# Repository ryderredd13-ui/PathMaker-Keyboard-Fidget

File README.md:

# PathMaker Keyboard Fidget
A Custom Keyboard fidget following the pathfinder guide renamed the PathMaker (Super original right?)
Anywayss... my spin on this project was to make it customizable!! i made a custom 3d case with extra space for stickers! I also added an extra button and led for extra fidget-ness :3

Here are some pics-

And heres my BOM-
[text](../../../Downloads/PathMaker-BOM.md)

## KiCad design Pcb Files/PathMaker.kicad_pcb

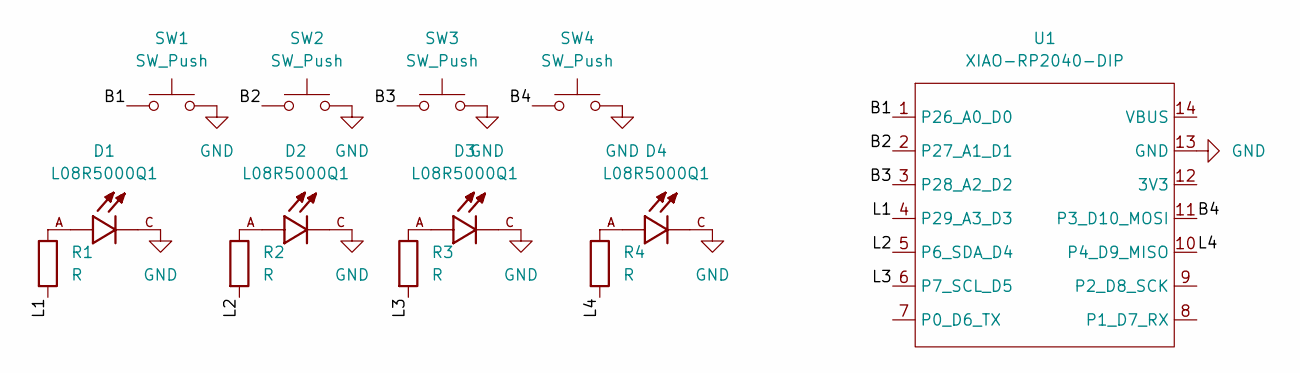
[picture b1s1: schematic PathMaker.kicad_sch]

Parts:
D1, D2, D3, D4: L08R5000Q1; LEDRD254W57D500H1070; PARTREV NA
R1, R2, R3, R4: R; R_Axial_DIN0204_L3.6mm_D1.6mm_P5.08mm_Horizontal
SW1, SW2, SW3, SW4: SW_Push; SW_Cherry_MX_1.00u_PCB
U1: XIAO-RP2040-DIP

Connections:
/B1: SW1.1, U1.1 (P26_A0_D0)
/B2: SW2.1, U1.2 (P27_A1_D1)
/B3: SW3.1, U1.3 (P28_A2_D2)
/B4: SW4.1, U1.11 (P3_D10_MOSI)
/L1: R1.2, U1.4 (P29_A3_D3)
/L2: R2.2, U1.5 (P6_SDA_D4)
/L3: R3.2, U1.6 (P7_SCL_D5)
/L4: R4.2, U1.10 (P4_D9_MISO)
GND: D1.C, D2.C, D3.C, D4.C, SW1.2, SW2.2, SW3.2, SW4.2, U1.13 (GND)
unnamed: D1.A, R1.1
unnamed: D2.A, R2.1
unnamed: D3.A, R3.1
unnamed: D4.A, R4.1

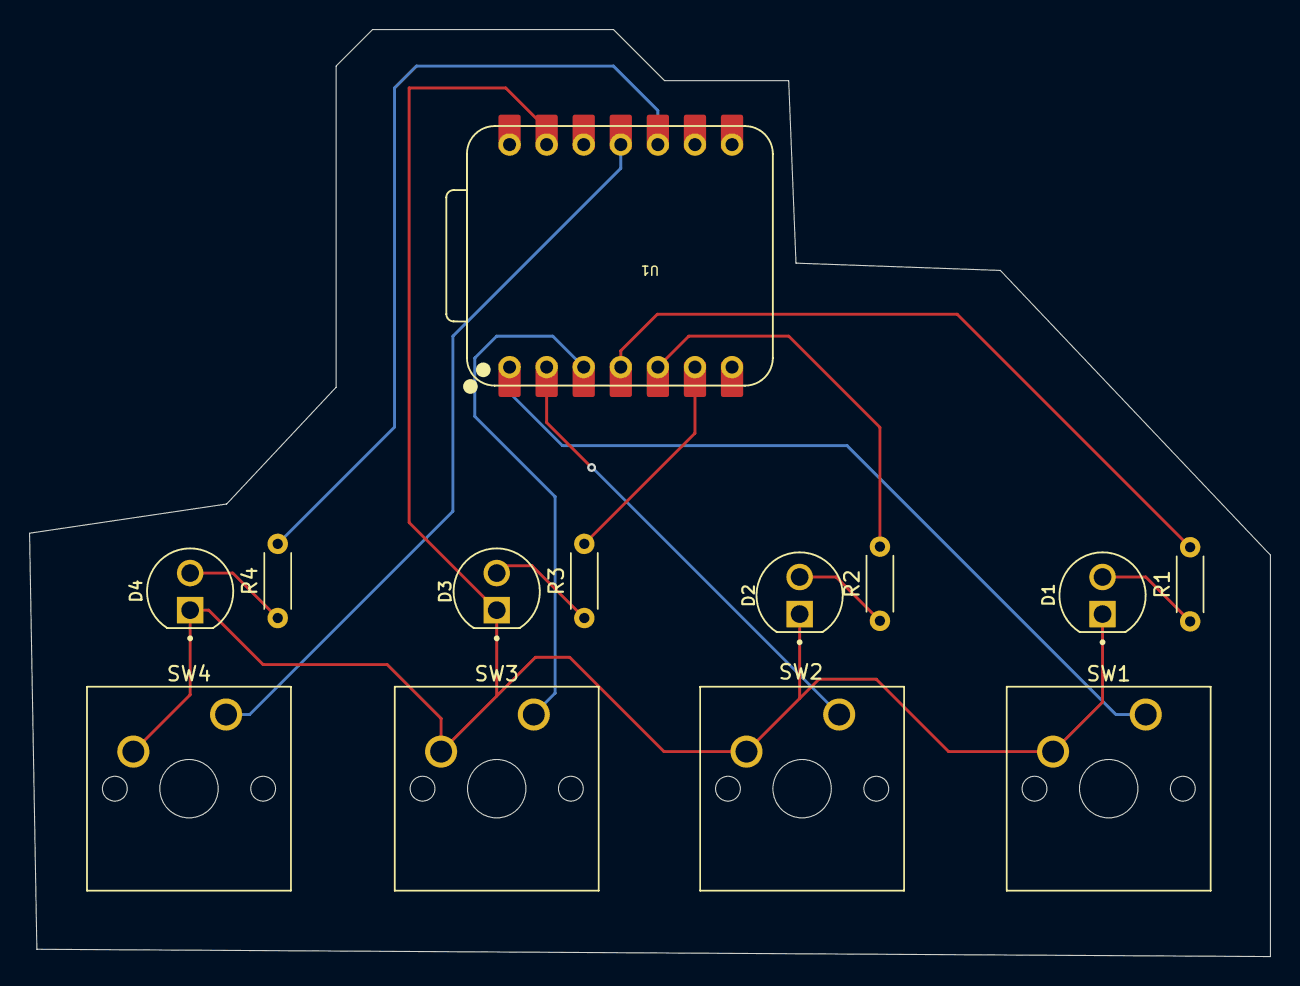
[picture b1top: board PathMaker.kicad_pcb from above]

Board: 2 copper layers, 85.0 x 63.5 mm, 13 parts (0 on the bottom side), 13 nets.

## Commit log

2026-05-04 uploading files from local repo
